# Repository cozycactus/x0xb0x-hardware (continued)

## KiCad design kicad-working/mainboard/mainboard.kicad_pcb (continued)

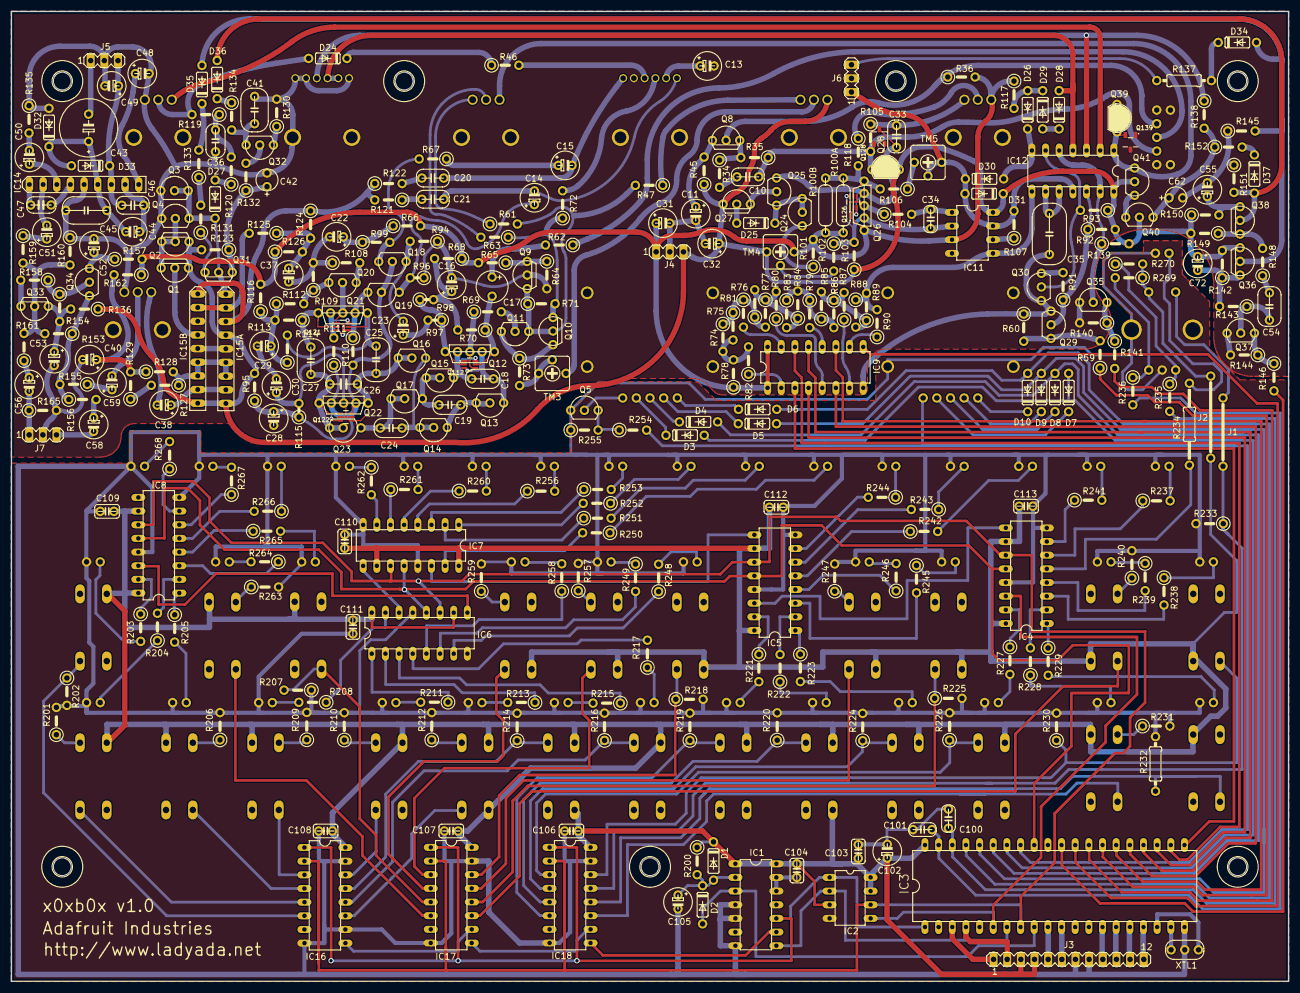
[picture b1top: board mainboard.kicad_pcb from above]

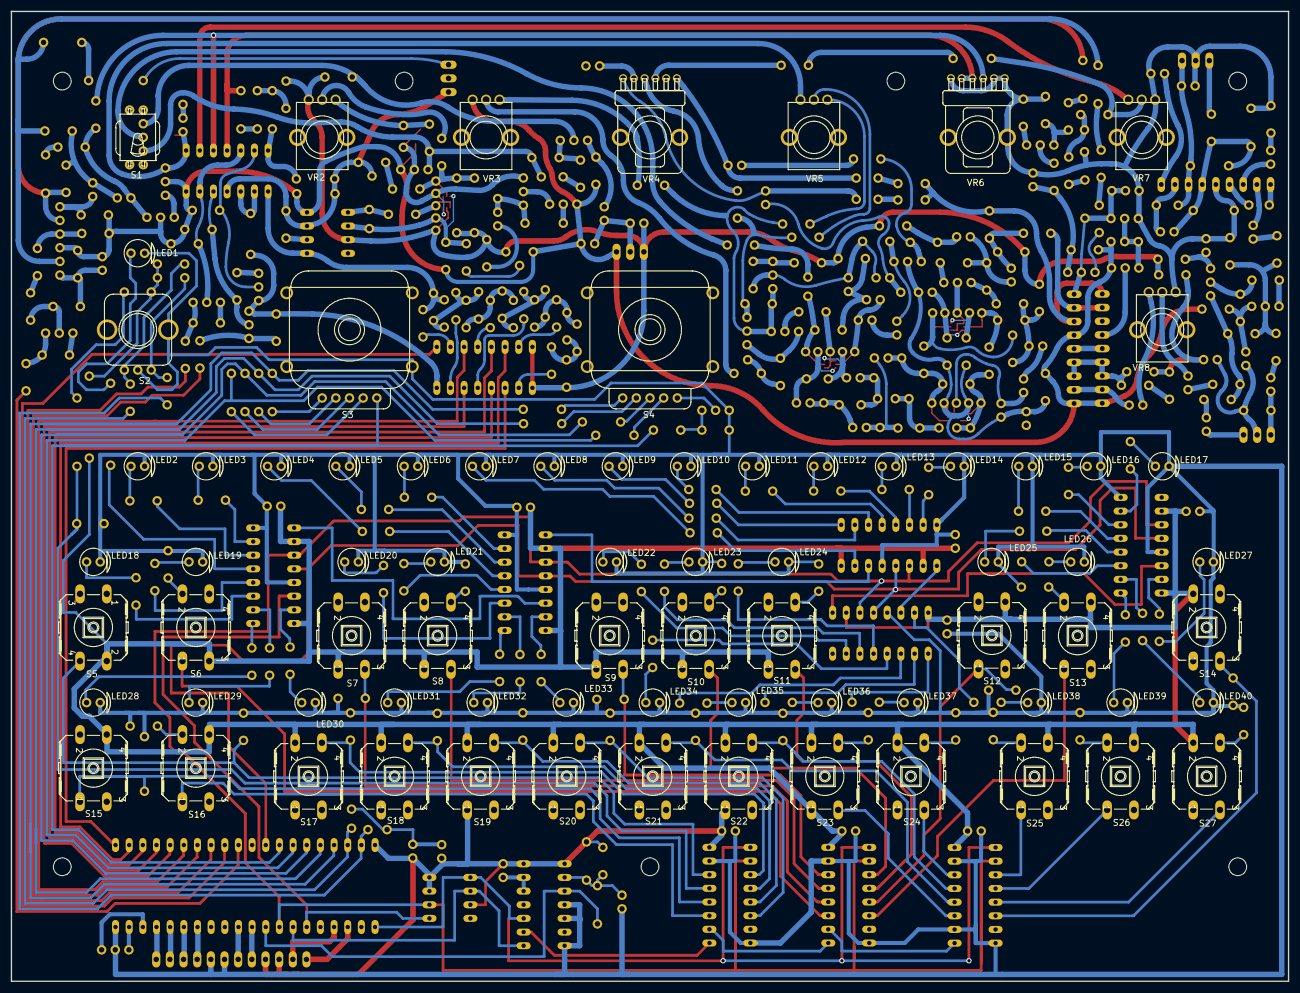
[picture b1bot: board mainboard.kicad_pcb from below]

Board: 2 copper layers, 237.5 x 180.3 mm, 423 parts (74 on the bottom side), 324 nets.

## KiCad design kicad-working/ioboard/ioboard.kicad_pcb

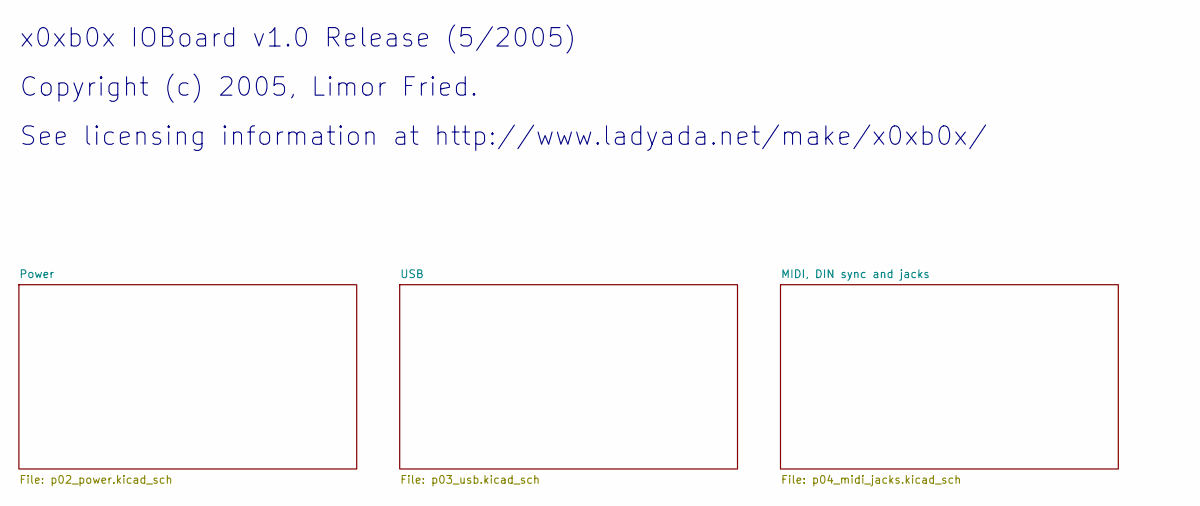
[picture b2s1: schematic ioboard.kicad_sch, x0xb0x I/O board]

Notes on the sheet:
x0xb0x IOBoard v1.0 Release (5/2005)
Copyright (c) 2005, Limor Fried.
See licensing information at http://www.ladyada.net/make/x0xb0x/

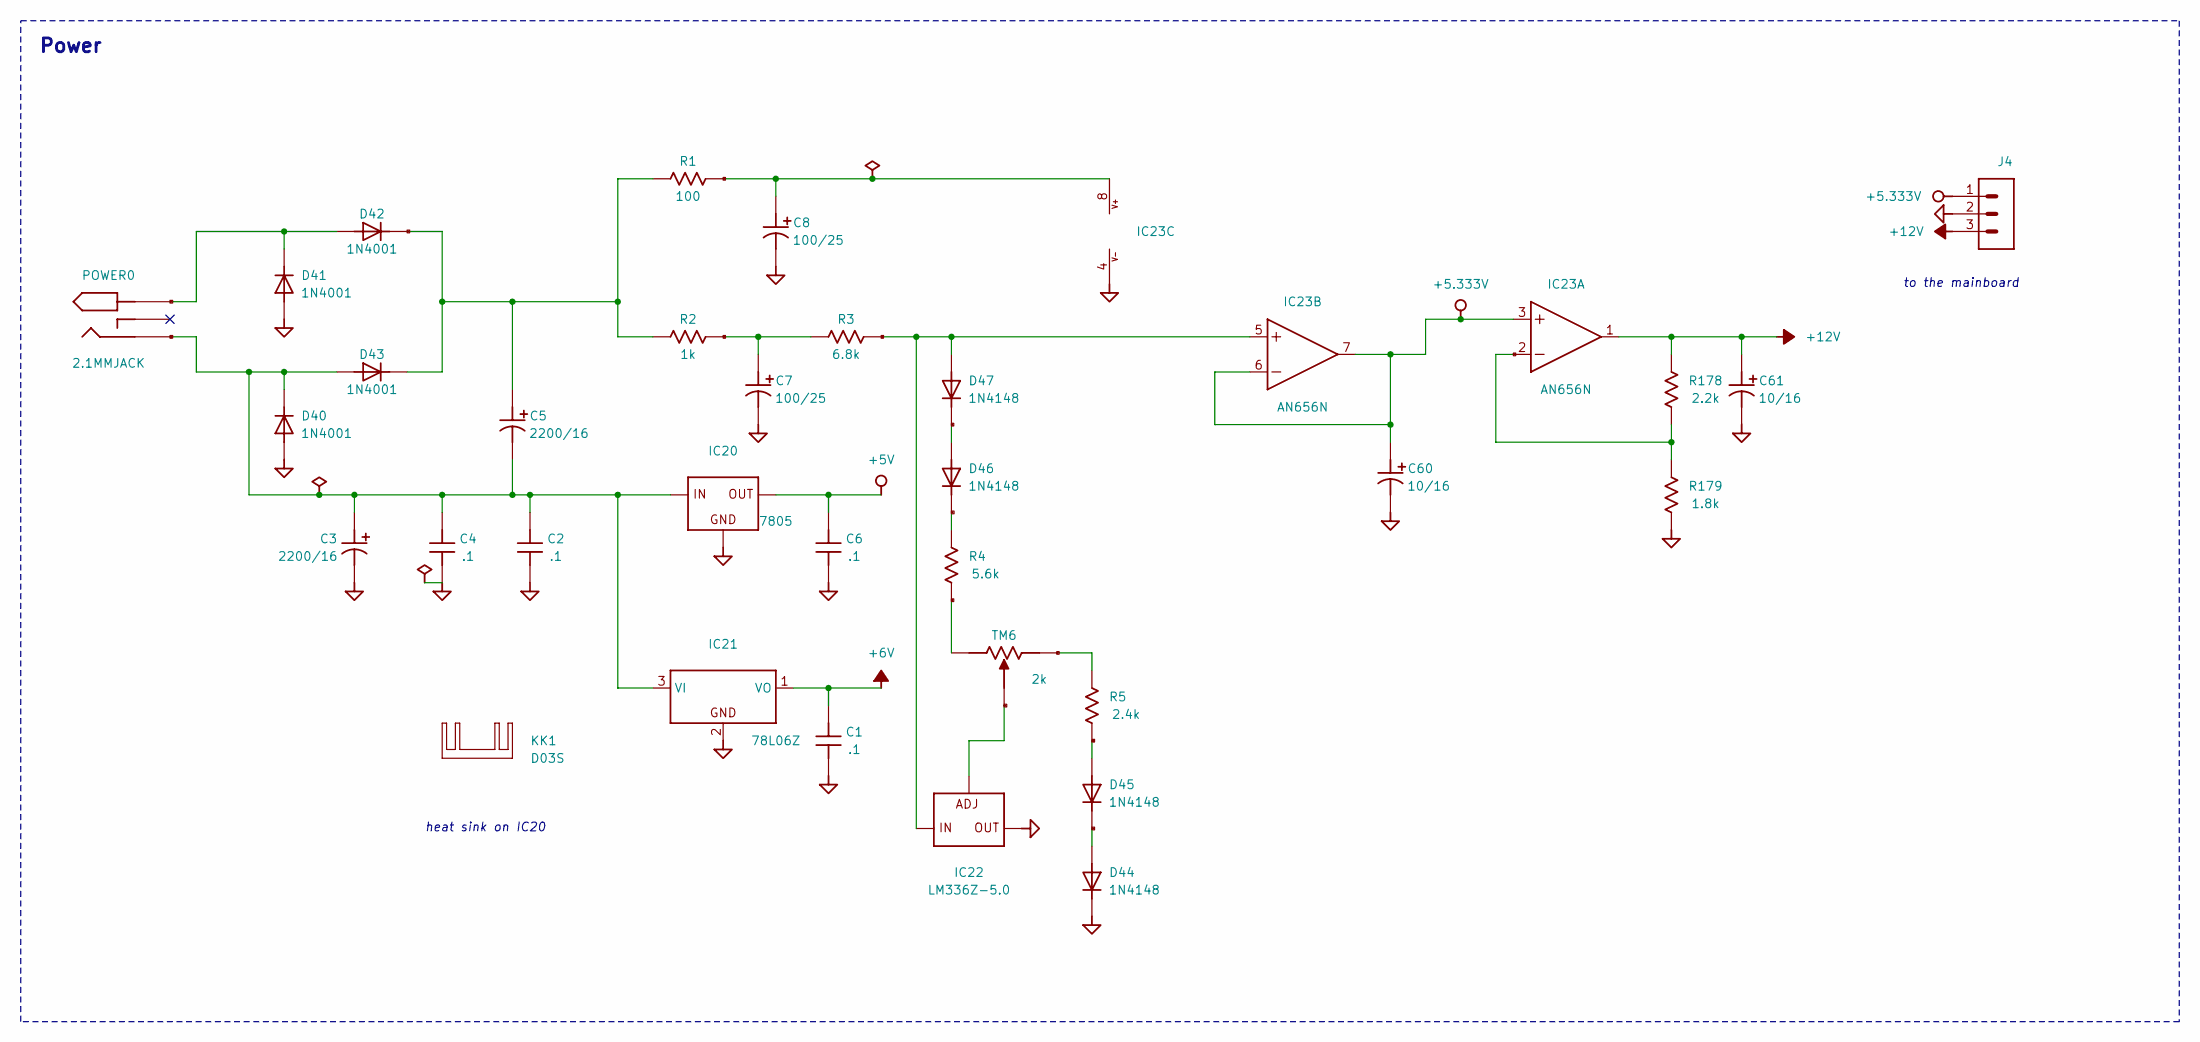
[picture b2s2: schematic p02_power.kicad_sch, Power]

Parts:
C1, C2, C4, C6: .1; C050H075X075
C3, C5: 2200/16; E5-13
C7, C8: 100/25; E5-6
C60, C61: 10/16; E5-6
D40, D41, D42, D43: 1N4001; DO41-10
D44, D45, D46, D47: 1N4148; DO35-10
IC20: 7805; 78XXS
IC21: 78L06Z; TO-92_x0x
IC22: LM336Z-5.0; TO-92_x0x
IC23: AN656N; DIL08
J4: MA03-''; MA03-1
KK1: D03S
POWER0: 2.1MMJACK; PJ-202AH
R1: 100; 0207_5V
R2: 1k; 0207_5V
R3: 6.8k; 0207_5V
R4: 5.6k; 0207_5V
R5: 2.4k; 0207_5V
R178: 2.2k; 0207_5V
R179: 1.8k; 0207_5V
TM6: 2k; 306

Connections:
+5.333V: C60.+, IC23.3 (+IN), IC23.6 (-IN), IC23.7 (OUT), J4.1
+5V: C6.1, IC20.OUT; also elsewhere on the board
+6V: C1.1, IC21.1 (VO); also elsewhere on the board
+12V: C61.+, IC23.1 (OUT), J4.3, R178.1
GND: C1.2, C2.2, C3.-, C4.2, C6.2, C7.-, C8.-, C60.-, C61.-, D40.A, D41.A, D44.C, IC20.GND, IC21.2 (GND), IC22.3 (A), IC23.4 (V-), J4.2, R179.2; also elsewhere on the board
unnamed: C8.+, IC23.8 (V+), R1.1
unnamed: D47.A, IC22.2 (K), IC23.5 (+IN), R3.2
unnamed: IC23.2 (-IN), R178.2, R179.1
unnamed: C7.+, R2.2, R3.1
unnamed: R4.1, TM6.3 (E)
unnamed: R5.2, TM6.1 (A)
unnamed: D46.A, D47.C
unnamed: D46.C, R4.2
unnamed: D45.A, R5.1
unnamed: D44.A, D45.C
unnamed: IC22.1 (ADJ), TM6.2 (S)
unnamed: D41.C, D42.A, POWER0.P$1
unnamed: C5.+, D42.C, D43.C, R1.2, R2.1
unnamed: C2.1, C3.+, C4.1, C5.-, D40.C, D43.A, IC20.IN, IC21.3 (VI), POWER0.P$2

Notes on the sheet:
Power
heat sink on IC20
to the mainboard

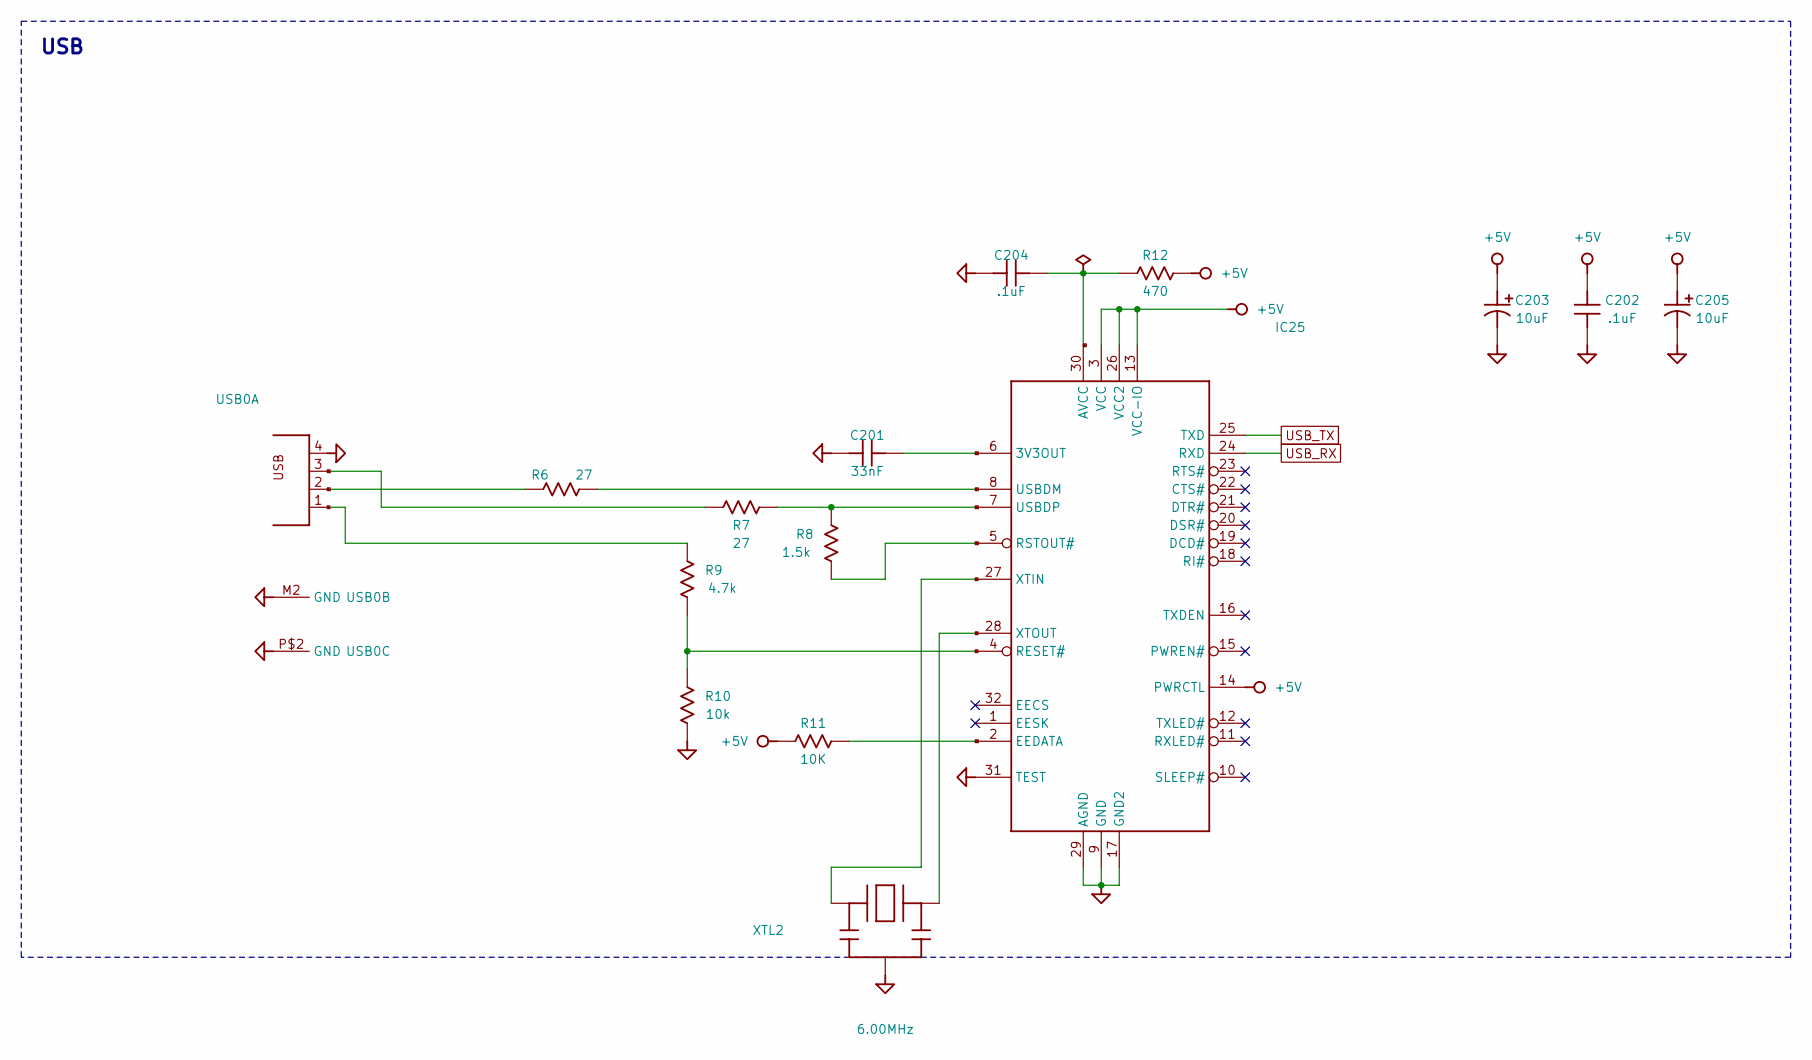
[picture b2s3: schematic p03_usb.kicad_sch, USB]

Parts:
C201: 33nF; C050-025X075
C202, C204: .1uF; C050H075X075
C203, C205: 10uF; E5-6
IC25: FT232; SQFP-S-7X7-32
R6, R7: 27; 0207_5V
R8: 1.5k; 0207_5V
R9: 4.7k; 0207_5V
R10: 10k; 0207_5V
R11: 10K; 0207_5V
R12: 470; 0207_5V
USB0: ACON_TYPEB''; PN61729
XTL2: 6.00MHz; Resonator_6MHz_x0x

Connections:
+5V: C202.1, C203.+, C205.+, IC25.3 (VCC), IC25.13 (VCC-IO), IC25.14 (PWRCTL), IC25.26 (VCC2), R11.2, R12.1; also elsewhere on the board
GND: C201.2, C202.2, C203.-, C204.2, C205.-, IC25.9 (GND), IC25.17 (GND2), IC25.29 (AGND), IC25.31 (TEST), R10.1, USB0.4, USB0.M2 (GND), USB0.P$2 (GND), XTL2.P$2 (GND); also elsewhere on the board
unnamed: R9.1, USB0.1
unnamed: IC25.27 (XTIN), XTL2.P$1 (IN)
unnamed: IC25.28 (XTOUT), XTL2.P$3 (OUT)
unnamed: IC25.4 (RESET#), R9.2, R10.2
unnamed: R6.2, USB0.2
unnamed: R7.1, USB0.3
unnamed: IC25.7 (USBDP), R7.2, R8.2
unnamed: IC25.8 (USBDM), R6.1
unnamed: IC25.5 (RSTOUT#), R8.1
unnamed: C201.1, IC25.6 (3V3OUT)
unnamed: C204.1, IC25.30 (AVCC), R12.2
unnamed: IC25.2 (EEDATA), R11.1
USB_RX: IC25.24 (RXD); also elsewhere on the board
USB_TX: IC25.25 (TXD); also elsewhere on the board

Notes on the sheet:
USB

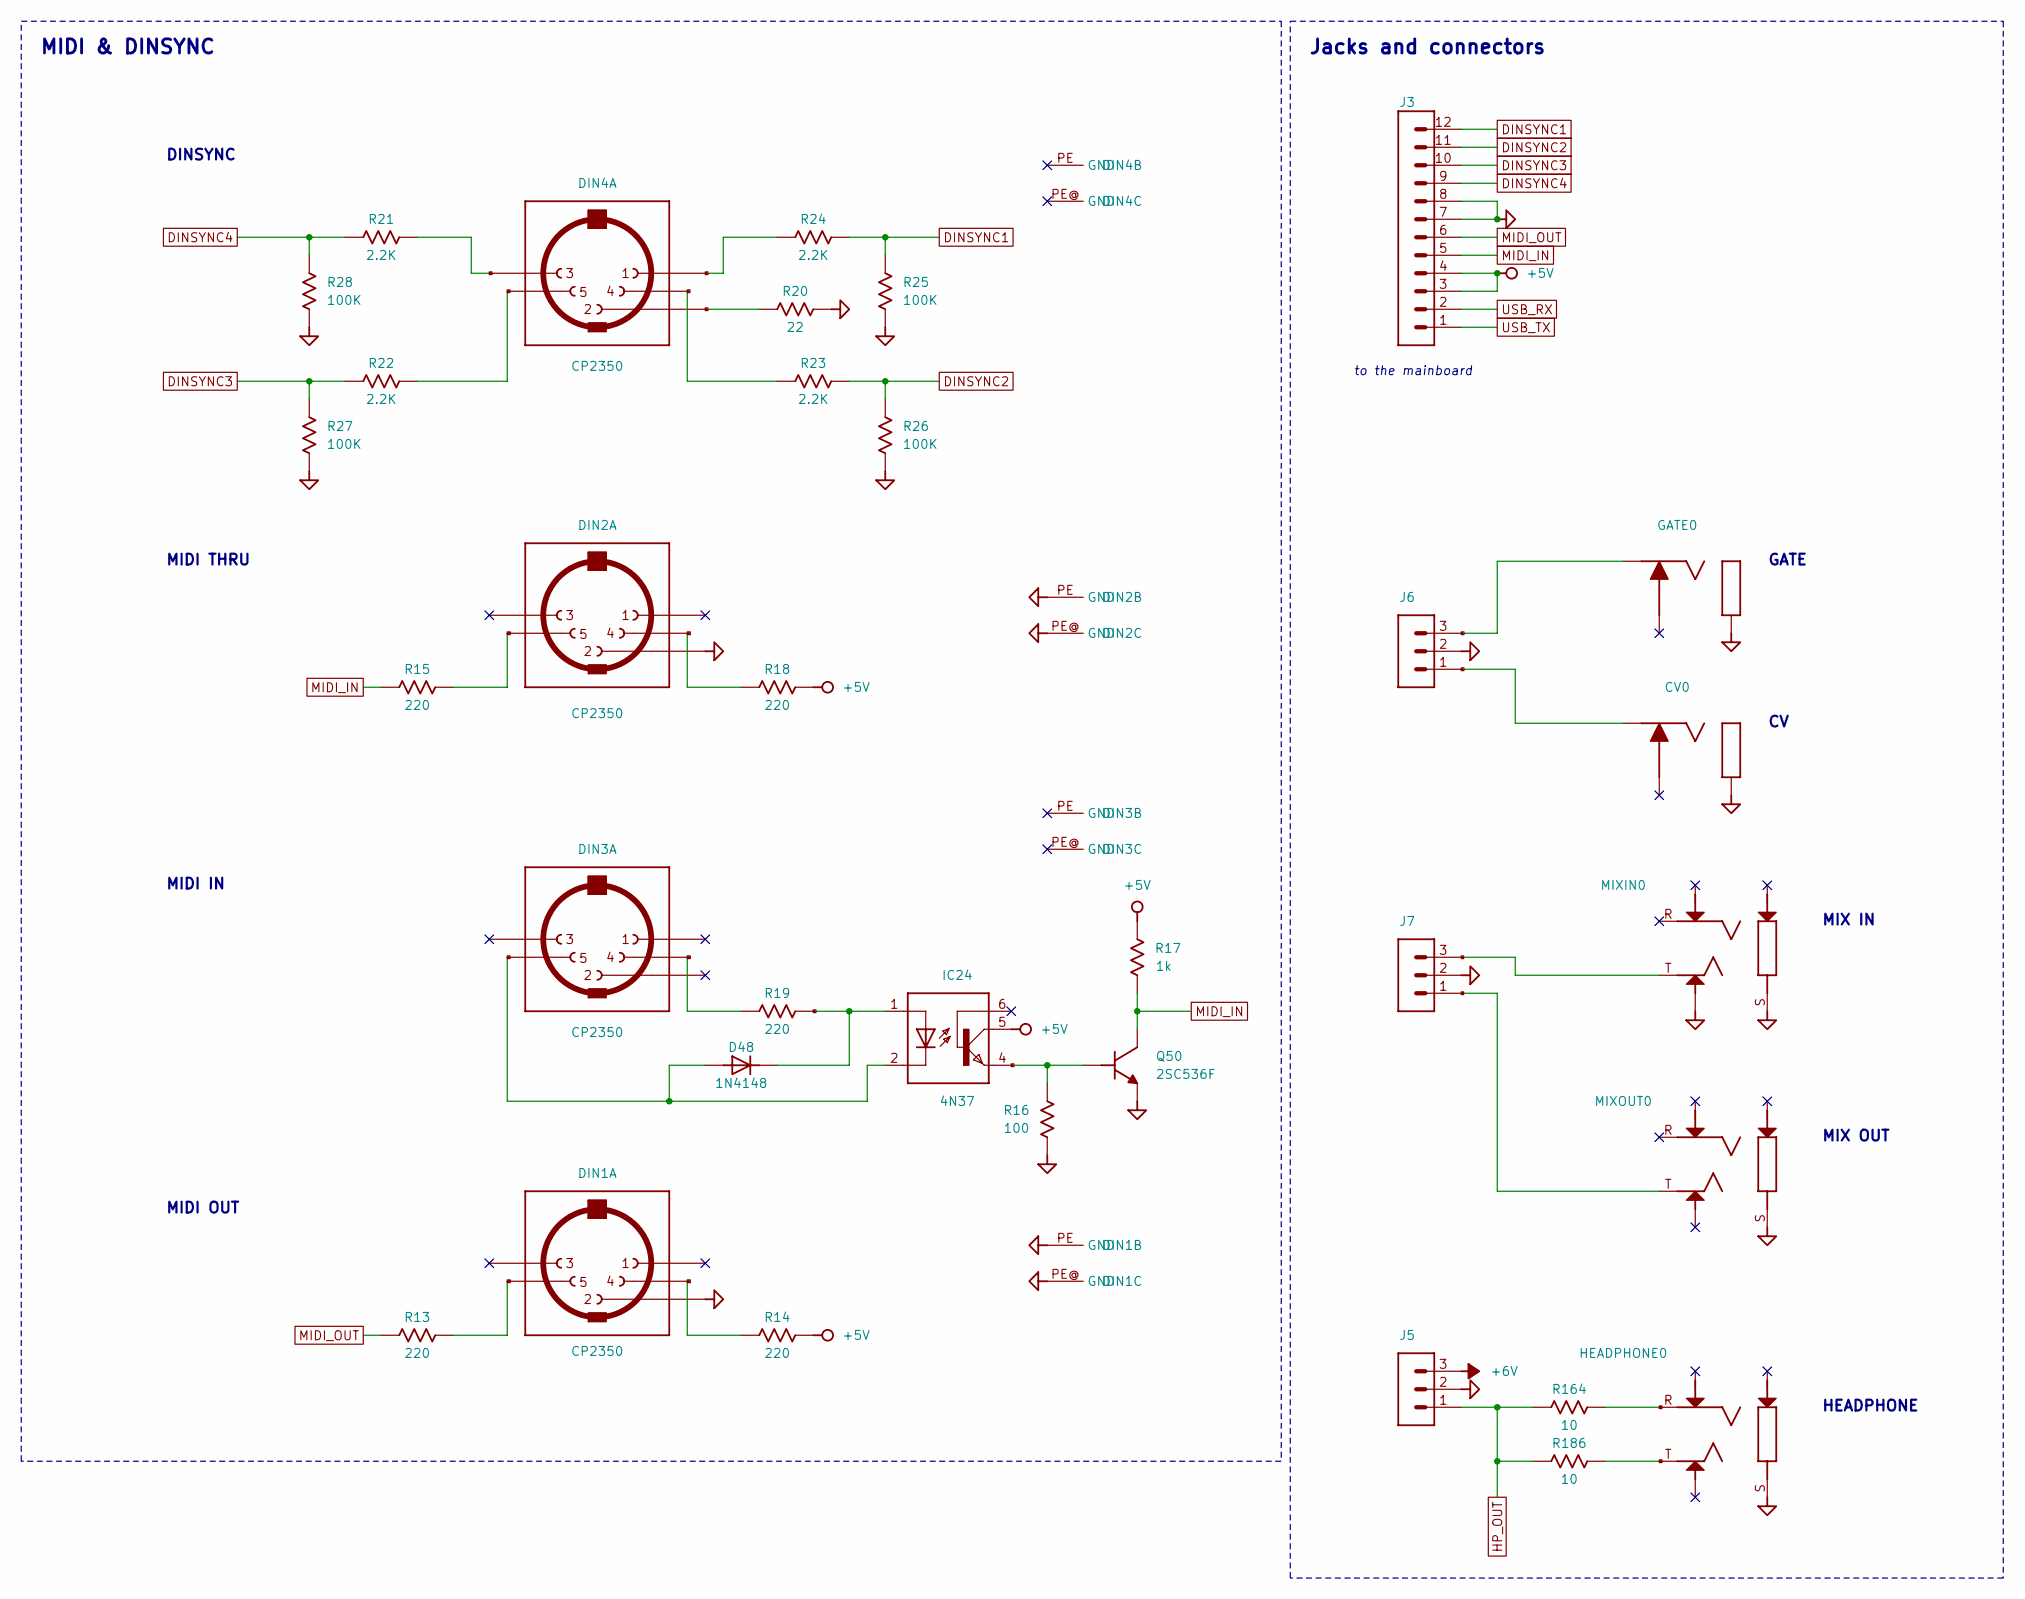
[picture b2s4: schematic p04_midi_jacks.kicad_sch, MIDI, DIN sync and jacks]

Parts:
CV0: MONO_CC; MJ-3536N
D48: 1N4148; DO35-10
DIN1, DIN2, DIN3, DIN4: CP2350; CP-2350
GATE0: MONO_CC; MJ-3536N
HEADPHONE0: NEUTRIX_STEREO; REAN_1_4STERO
IC24: 4N37; DIL06
J3: MA12-''; MA12-1
J5, J6, J7: MA03-''; MA03-1
MIXIN0: NEUTRIX_STEREO; REAN_1_4STERO
MIXOUT0: NEUTRIX_STEREO; REAN_1_4STERO
Q50: 2SC536F
R13, R14, R15, R18, R19: 220; 0207_5V
R16: 100; 0207_5V
R17: 1k; 0207_5V
R20: 22; 0207_5V
R21, R22, R23, R24: 2.2K; 0207_5V
R25, R26, R27, R28: 100K; 0207_5V
R164, R186: 10; 0207_5V

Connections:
+5V: IC24.5 (COL), J3.3, J3.4, R14.2, R17.2, R18.2; also elsewhere on the board
+6V: J5.3; also elsewhere on the board
DINSYNC1: J3.12, R24.1, R25.2
DINSYNC2: J3.11, R23.2, R26.1
DINSYNC3: J3.10, R22.1, R27.1
DINSYNC4: J3.9, R21.2, R28.2
GND: CV0.SLEEVE, DIN1.2, DIN1.PE (GND), DIN1.PE@ (GND), DIN2.2, DIN2.PE (GND), DIN2.PE@ (GND), GATE0.SLEEVE, HEADPHONE0.S, J3.7, J3.8, J5.2, J6.2, J7.2, MIXIN0.S, MIXIN0.TN, MIXOUT0.S, Q50.3 (E), R16.1, R20.2, R25.1, R26.2, R27.2, R28.1; also elsewhere on the board
HP_OUT: J5.1, R164.1, R186.1
MIDI_IN: J3.5, Q50.2 (C), R15.2, R17.1
MIDI_OUT: J3.6, R13.1
unnamed: J7.1, MIXOUT0.T
unnamed: J7.3, MIXIN0.T
unnamed: IC24.4 (EMI), Q50.1 (B), R16.2
unnamed: DIN4.3, R21.1
unnamed: DIN4.5, R22.2
unnamed: DIN4.1, R24.2
unnamed: DIN4.4, R23.1
unnamed: GATE0.TIP, J6.3
unnamed: CV0.TIP, J6.1
unnamed: HEADPHONE0.R, R164.2
unnamed: HEADPHONE0.T, R186.2
unnamed: DIN4.2, R20.1
unnamed: D48.A, DIN3.5, IC24.2 (C)
unnamed: D48.C, IC24.1 (A), R19.2
unnamed: DIN3.4, R19.1
unnamed: DIN2.5, R15.1
unnamed: DIN2.4, R18.1
unnamed: DIN1.5, R13.2
unnamed: DIN1.4, R14.1
USB_RX: J3.2; also elsewhere on the board
USB_TX: J3.1; also elsewhere on the board

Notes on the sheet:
MIDI & DINSYNC
Jacks and connectors
DINSYNC
MIDI THRU
MIDI IN
MIDI OUT
to the mainboard
GATE
MIX IN
MIX OUT
HEADPHONE

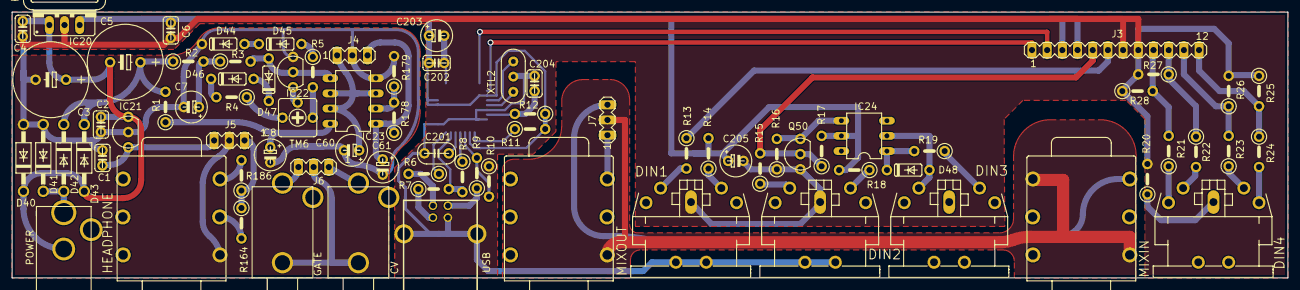
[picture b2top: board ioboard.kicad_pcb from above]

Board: 2 copper layers, 213.4 x 44.5 mm, 82 parts (1 on the bottom side), 59 nets.

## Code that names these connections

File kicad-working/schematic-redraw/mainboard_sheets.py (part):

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    d.flag((76.2, 99.06))

    # The MCU's lines, named as on the original sheet.
    for pin_no, net in ((32, 'LED_LATCH'), (33, 'ROTARYCOM3'), (34, 'ROTARY1'), (35, 'ROTARY2'), (36, 'ROTARY4'), (37, 'ROTARY8'), (38, 'TEMPO_SW_A'), (39, 'TEMPO_SW_B'),
                        (8, 'SPI_CLK'), (7, 'SPI_OUT'), (6, 'SPI_IN'), (4, 'USB_TX'), (3, 'USBRX'), (1, 'SWITCH_LATCH'),
                        (28, 'ACCENT'), (27, 'SLIDE'), (26, 'NOTE5'), (25, 'NOTE4'), (24, 'NOTE3'), (23, 'NOTE2'), (22, 'NOTE1'), (21, 'NOTE0'),
                        (17, 'DINSYNC1'), (16, 'DINSYNC2'), (15, 'DINSYNC3'), (14, 'DINSYNC4'), (11, 'MIDI_OUT'), (10, 'MIDI_IN'),
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
    # The connector to the I/O board.
    d.chip('J3', "MA12-''", 1, 287.02, 160.02, ref_at=(287.02, 141.0), hide_value=True)
    for pin_no, net in ((12, 'DINSYNC1'), (11, 'DINSYNC2'), (10, 'DINSYNC3'), (9, 'DINSYNC4'), (6, 'MIDI_OUT'), (5, 'MIDI_IN'), (2, 'USB_TX'), (1, 'USBRX')):
        d.out(f'J3.{pin_no}', net, 'R', 5.08)
    d.route('J3.8', (299.72, 154.94), (299.72, 157.48), 'J3.7')
    d.ground((299.72, 157.48), 'R')
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    d.ground('R255.1', 'L')
    d.route('R254.2', (27.94, 142.24), (71.12, 142.24), 'S3.C')
    d.route((27.94, 142.24), (27.94, 152.4))
    d.label('ROTARYCOM3', (27.94, 152.4), 'B')

    # The tempo encoder.
    d.note('tempo', 142.24, 35.56)
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    d.across('J1', 190.5, 43.18, '1')
    d.route((185.42, 43.18), 'J1.1')
    d.route('J1.2', (218.44, 43.18))
    d.label('TEMPO_SW', (218.44, 43.18))
    d.down('R233', 208.28, 50.8, '1')
    d.route((208.28, 43.18), 'R233.1')
    d.ground('R233.2')
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    d.down('C101', 187.96, 99.06, '2', left_text=True)
    d.ground('C101.1')
    d.route((165.1, 86.36), (205.74, 86.36))
    d.label('TEMPO_SW_A', (205.74, 86.36))
    d.route((187.96, 81.28), (205.74, 81.28))
    d.label('TEMPO_SW_B', (205.74, 81.28))


SWITCH_ROWS = (
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    d.route((22.86, 93.98), (22.86, 190.5))
    d.route((20.32, 96.52), (20.32, 193.04))
    d.route((22.86, 190.5), (15.24, 190.5))
    d.label('SPI_CLK', (15.24, 190.5), 'L')
    d.route((20.32, 193.04), (15.24, 193.04))
    d.label('LED_LATCH', (15.24, 193.04), 'L')
    # The chain: SPI_IN into IC4, each QH* into the next SER.
    d.route('IC4.14', (30.48, 55.88), (30.48, 40.64))
    d.label('SPI_IN', (30.48, 40.64), 'L')
    for a, b, x in (('IC4', 'IC5', 58.42), ('IC5', 'IC7', 180.34)):
        nx = x + 121.92
        d.route(f'{a}.9', (x + 13.97, 78.74), (x + 13.97, 91.44), (nx - 27.94, 91.44), (nx - 27.94, 55.88), f'{b}.14')
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    d.dx, d.dy = 2.54, 12.7
    # The note latch and its resistor ladder: six bits into a 200K R-2R network.
    d.chip('IC9', '4174P', 1, 45.72, 83.82, ref_at=(38.1, 68.58), val_at=(45.72, 99.06))
    for pin_no, net in ((3, 'NOTE0'), (4, 'NOTE2'), (6, 'NOTE4'), (11, 'NOTE5'), (13, 'NOTE3'), (14, 'NOTE1'), (9, 'NOTE_LATCH')):
        d.out(f'IC9.{pin_no}', net, 'L', 5.08)
    d.rail('+5.333V', 'IC9.1', 'L')
    d.chip('IC9', '4174P', 2, 25.4, 45.72, ref_at=(30.48, 45.72), hide_value=True, just='left')
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    d.block('ENV', 12.7, 10.16, 310.0, 180.0)

    # The gate turns on Q37, Q36 and the VCA envelope.
    d.label('GATE', (33.02, 71.12), 'L')
    d.across('R146', 45.72, 71.12, '2')
    d.route((33.02, 71.12), 'R146.2')
    d.down('R144', 53.34, 78.74, '1')
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
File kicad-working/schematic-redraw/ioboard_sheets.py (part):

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    d.route('R21.2', (60.96, 50.8), 'R28.2')
    d.ground('R28.1')
    d.route((60.96, 50.8), (50.8, 50.8))
    d.label('DINSYNC4', (50.8, 50.8), 'L')
    d.across('R22', 71.12, 71.12, '1')
    d.route('DIN4.5', (88.9, 71.12), 'R22.2')
    d.down('R27', 60.96, 78.74, '1')
    d.route('R22.1', (60.96, 71.12), 'R27.1')
    d.ground('R27.2')
    d.route((60.96, 71.12), (50.8, 71.12))
    d.label('DINSYNC3', (50.8, 71.12), 'L')
    d.across('R24', 132.08, 50.8, '2')
    d.route('DIN4.1', (119.38, 55.88), (119.38, 50.8), 'R24.2')
    d.down('R25', 142.24, 58.42, '2')
    d.route('R24.1', (142.24, 50.8), 'R25.2')
    d.ground('R25.1')
    d.route((142.24, 50.8), (149.86, 50.8))
    d.label('DINSYNC1', (149.86, 50.8), 'R')
    d.across('R23', 132.08, 71.12, '1')
    d.route('DIN4.4', (114.3, 71.12), 'R23.1')
    d.down('R26', 142.24, 78.74, '1')
    d.route('R23.2', (142.24, 71.12), 'R26.1')
    d.ground('R26.2')
    d.route((142.24, 71.12), (149.86, 71.12))
    d.label('DINSYNC2', (149.86, 71.12), 'R')
    d.across('R20', 129.54, 60.96, '1')
    d.route('DIN4.2', 'R20.1')
    d.ground('R20.2', 'R')
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    d.rail('+5V', 'R17.2')
    d.route('R17.1', 'Q50.2')
    d.route((177.8, 160.02), (185.42, 160.02))
    d.label('MIDI_IN', (185.42, 160.02), 'R')

    # MIDI out.
    d.caption('MIDI OUT', 40.64, 187.96)
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
    # The connector to the mainboard.
    d.chip('J3', "MA12-''", 1, 215.9, 50.8, ref_at=(215.9, 31.75), hide_value=True)
    for pin_no, net in ((12, 'DINSYNC1'), (11, 'DINSYNC2'), (10, 'DINSYNC3'), (9, 'DINSYNC4'), (6, 'MIDI_OUT'), (5, 'MIDI_IN'), (2, 'USB_RX'), (1, 'USB_TX')):
        d.out(f'J3.{pin_no}', net, 'R', 5.08)
    d.route('J3.8', (228.6, 45.72), (228.6, 48.26), 'J3.7')
    d.ground((228.6, 48.26), 'R')
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    d.route((228.6, 215.9), (228.6, 223.52), 'R186.1')
    d.route('R186.2', 'HEADPHONE0.T')
    d.route((228.6, 223.52), (228.6, 228.6))
    d.label('HP_OUT', (228.6, 228.6), 'B')
    d.ground('HEADPHONE0.S')
    for pad in ('RN', 'SN', 'TN'):
        d.nc(f'HEADPHONE0.{pad}')
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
